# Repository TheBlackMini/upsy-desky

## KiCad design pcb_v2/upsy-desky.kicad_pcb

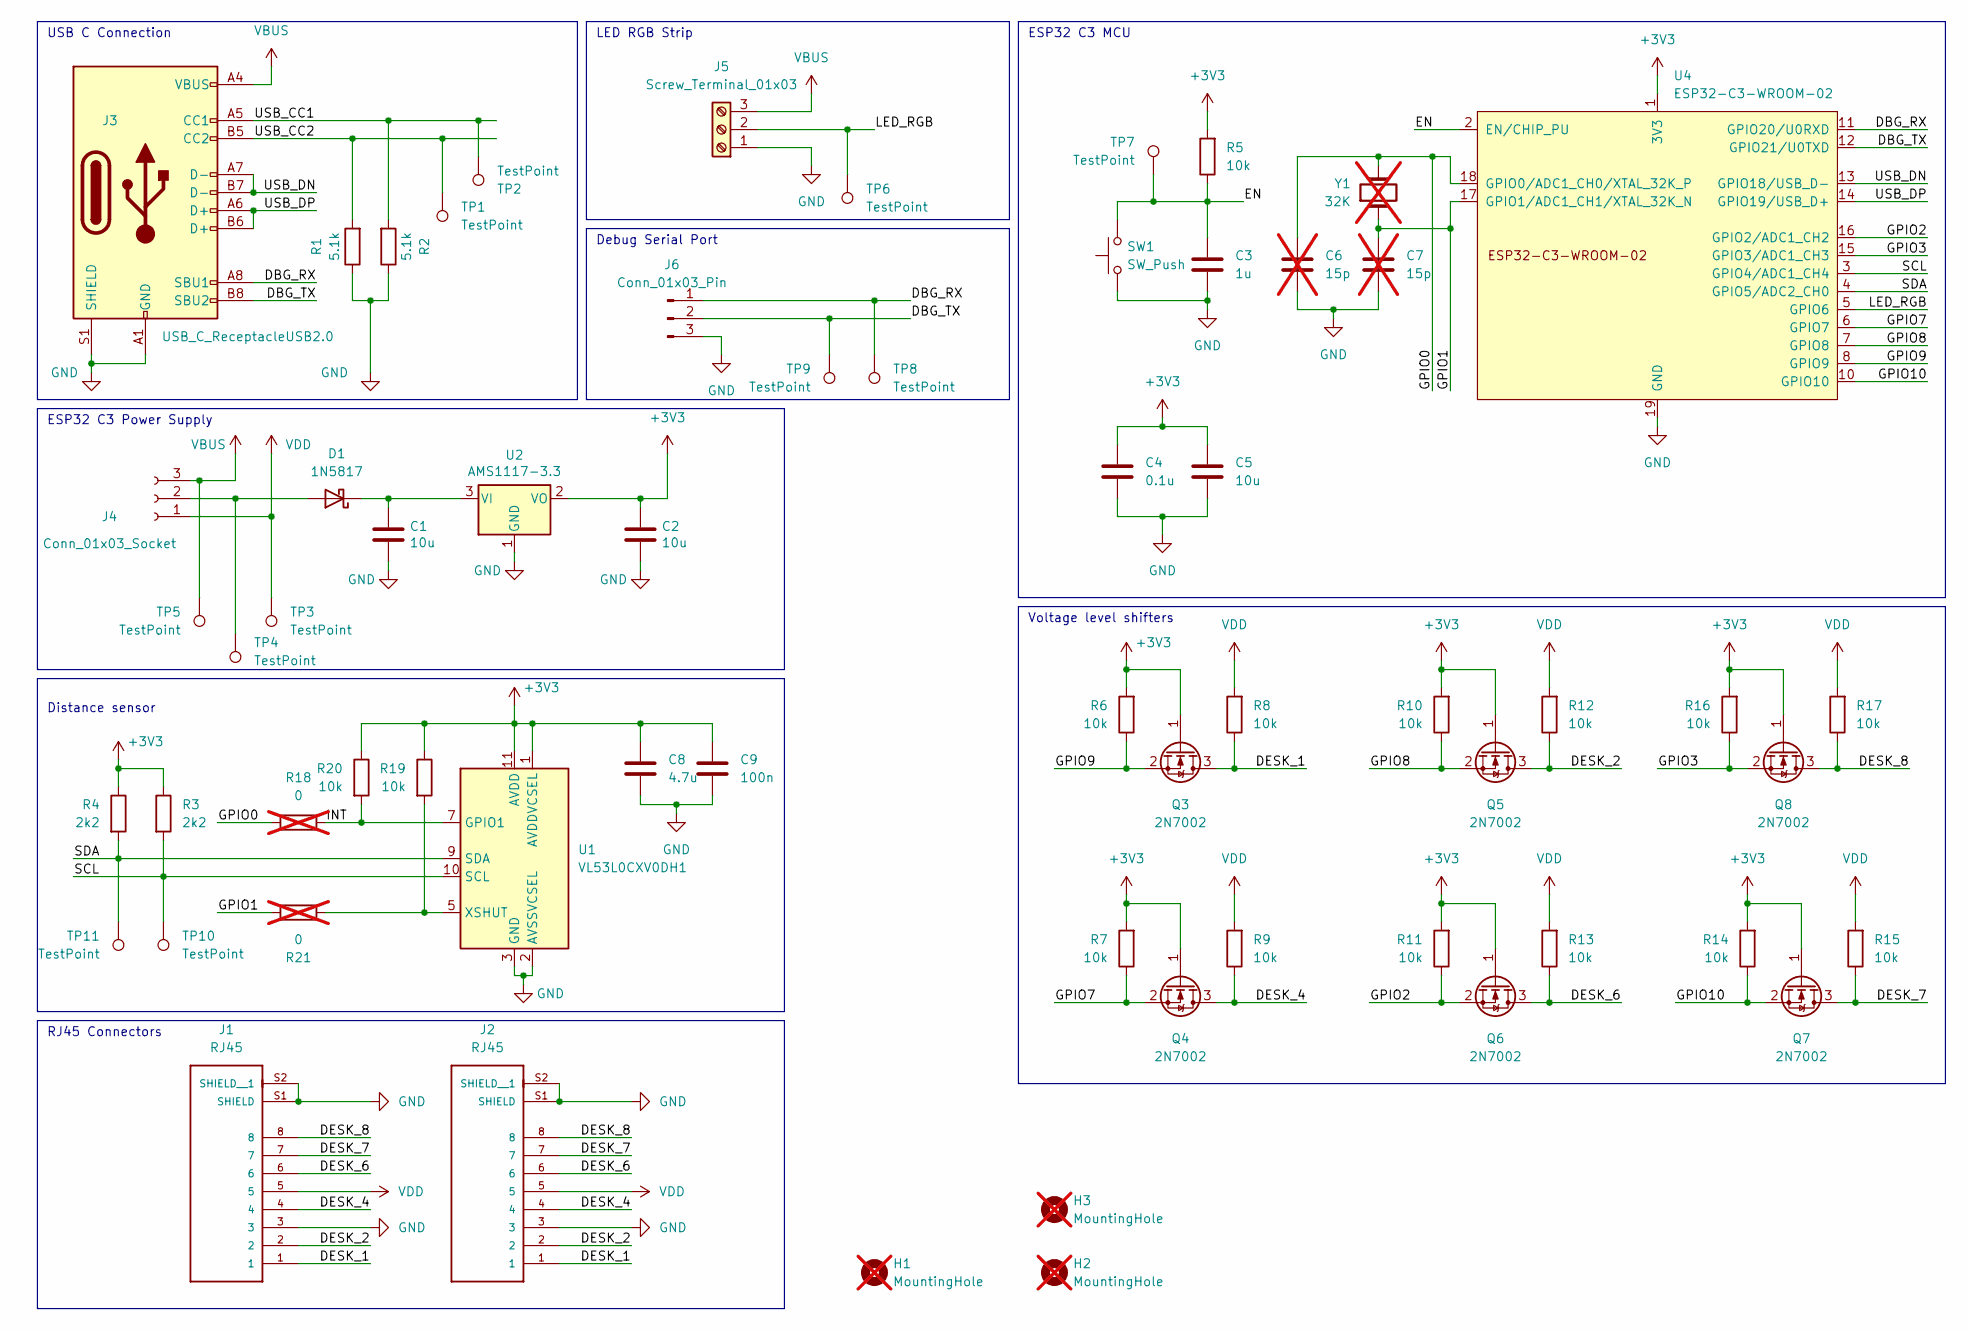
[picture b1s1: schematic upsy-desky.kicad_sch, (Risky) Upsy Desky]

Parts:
C1, C2, C5: 10u; C_0402_1005Metric; MPN GRM155R60J106ME05J; LCSC C15525
C3: 1u; C_0402_1005Metric; MPN 0402W105K100HI; LCSC C52923
C4: 0.1u; C_0402_1005Metric; MPN 0402B104K160HI; LCSC C1525
C6, C7: 15p; C_0402_1005Metric; MPN TCC0402COG150J500AT; not fitted
C8: 4.7u; C_0402_1005Metric; MPN CL05A475MQ5NRNC; DigiKey 1276-1056-2-ND
C9: 100n; C_0402_1005Metric; MPN CC0402KRX7R6BB104; DigiKey 311-1345-2-ND
D1: 1N5817; D_SOD-323; MPN B5817WS-TP; LCSC C191023
H1, H2, H3: MountingHole; MountingHole_2.2mm_M2_Pad; not fitted
J1, J2: RJ45; RJ45_Amphenol_54602-x08_Horizontal; PARTREV 00; LCSC C708595
J3: USB_C_ReceptacleUSB2.0; USB_C_Receptacle_Palconn_UTC16-G; MPN TYPE-C-31-M-12; LCSC C165948
J4: Conn_01x03_Socket; FanPinHeader_1x03_P2.54mm_Vertical; MPN 0022272031; DigiKey WM4112-ND
J5: Screw_Terminal_01x03; TerminalBlock_Altech_AK300-3_P5.00mm; MPN 30-003; DigiKey 1920-30.003-ND
J6: Conn_01x03_Pin; JST_EH_B3B-EH-A_1x03_P2.50mm_Vertical; MPN B3B-EH-A; DigiKey 455-B3B-EH-A-ND
Q3, Q4, Q5, Q6, Q7, Q8: 2N7002; SOT-23; MPN 2N7002; LCSC C8545
R1, R2: 5.1k; R_0402_1005Metric; MPN CR0402JC5K1S01; LCSC C25905
R3, R4: 2k2; R_0402_1005Metric; MPN RC0402FR-072K2L; DigiKey 311-2.20KLRTR-ND
R5, R6, R7, R8, R9, R10, R11, R12, R13, R14, R15, R16, R17: 10k; R_0402_1005Metric; MPN RC0402JR-1310KL; LCSC C25744
R18, R21: 0; R_0402_1005Metric; not fitted
R19, R20: 10k; R_0402_1005Metric; MPN RC0402JR-1310KL; DigiKey 13-RC0402JR-1310KLTR-ND
SW1: SW_Push; SW_Push_1P1T_NO_CK_KMR2; MPN KMR223GLFG; DigiKey 401-1428-2-ND
TP1, TP2, TP3, TP4, TP5, TP6, TP7, TP8, TP9, TP10, TP11: TestPoint; TestPoint_Pad_D1.0mm
U1: VL53L0CXV0DH1; ST_VL53L1x; MPN VL53L0CXV0DH/1; DigiKey 497-16538-2-ND
U2: AMS1117-3.3; SOT-223-3_TabPin2; MPN AMS1117-3.3; LCSC C6186
U4: ESP32-C3-WROOM-02; MPN ESP32-C3-WROOM-02-N4; DigiKey 1965-ESP32-C3-WROOM-02-N4TR-ND
Y1: 32K; Crystal_SMD_2012-2Pin_2.0x1.2mm; MPN 9HT11-32-768KDZF-T; DigiKey 887-1425-2-ND; not fitted

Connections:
+3V3: C2.1, C4.1, C5.1, C8.1, C9.1, Q3.1 (G), Q4.1 (G), Q5.1 (G), Q6.1 (G), Q7.1 (G), Q8.1 (G), R3.1, R4.1, R5.2, R6.2, R7.2, R10.2, R11.2, R14.2, R16.2, R19.1, R20.1, U1.1 (AVDDVCSEL), U1.11 (AVDD), U2.2 (VO), U4.1 (3V3)
/DBG_RX: J3.A8 (SBU1), J6.1, TP8.1, U4.11 (GPIO20/U0RXD)
/DBG_TX: J3.B8 (SBU2), J6.2, TP9.1, U4.12 (GPIO21/U0TXD)
/DESK_1: J1.1, J2.1, Q3.3 (D), R8.1
/DESK_2: J1.2, J2.2, Q5.3 (D), R12.1
/DESK_4: J1.4, J2.4, Q4.3 (D), R9.1
/DESK_6: J1.6, J2.6, Q6.3 (D), R13.1
/DESK_7: J1.7, J2.7, Q7.3 (D), R15.1
/DESK_8: J1.8, J2.8, Q8.3 (D), R17.1
/EN: C3.1, R5.1, SW1.2, TP7.1, U4.2 (EN/CHIP_PU)
/GPIO0: C6.1, R18.2, U4.18 (GPIO0/ADC1_CH0/XTAL_32K_P), Y1.2
/GPIO1: C7.1, R21.2, U4.17 (GPIO1/ADC1_CH1/XTAL_32K_N), Y1.1
/GPIO2: Q6.2 (S), R11.1, U4.16 (GPIO2/ADC1_CH2)
/GPIO3: Q8.2 (S), R16.1, U4.15 (GPIO3/ADC1_CH3)
/GPIO7: Q4.2 (S), R7.1, U4.6 (GPIO7)
/GPIO8: Q5.2 (S), R10.1, U4.7 (GPIO8)
/GPIO9: Q3.2 (S), R6.1, U4.8 (GPIO9)
/GPIO10: Q7.2 (S), R14.1, U4.10 (GPIO10)
/INT: R18.1, R20.2, U1.7 (GPIO1)
/LED_RGB: J5.2, TP6.1, U4.5 (GPIO6)
/SCL: R3.2, TP10.1, U1.10 (SCL), U4.3 (GPIO4/ADC1_CH4)
/SDA: R4.2, TP11.1, U1.9 (SDA), U4.4 (GPIO5/ADC2_CH0)
/USB_CC1: J3.A5 (CC1), R2.2, TP2.1
/USB_CC2: J3.B5 (CC2), R1.2, TP1.1
/USB_DN: J3.A7 (D-), J3.B7 (D-), U4.13 (GPIO18/USB_D-)
/USB_DP: J3.A6 (D+), J3.B6 (D+), U4.14 (GPIO19/USB_D+)
GND: C1.2, C2.2, C3.2, C4.2, C5.2, C6.2, C7.2, C8.2, C9.2, J1.3, J1.S1 (SHIELD), J1.S2 (SHIELD__1), J2.3, J2.S1 (SHIELD), J2.S2 (SHIELD__1), J3.A1 (GND), J3.A12 (GND), J3.B1 (GND), J3.B12 (GND), J3.S1 (SHIELD), J5.1, J6.3, R1.1, R2.1, SW1.1, U1.2 (AVSSVCSEL), U1.3 (GND), U1.4 (GND), U1.6 (GND), U1.12 (GND), U2.1 (GND), U4.9 (GND), U4.19 (GND)
unnamed: D1.2 (A), J4.2, TP4.1
unnamed: C1.1, D1.1 (K), U2.3 (VI)
unnamed: R19.2, R21.1, U1.5 (XSHUT)
VBUS: J3.A4 (VBUS), J3.A9 (VBUS), J3.B4 (VBUS), J3.B9 (VBUS), J4.3, J5.3, TP5.1
VDD: J1.5, J2.5, J4.1, R8.2, R9.2, R12.2, R13.2, R15.2, R17.2, TP3.1

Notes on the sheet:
ESP32 C3 MCU
Debug Serial Port
RJ45 Connectors
USB C Connection
LED RGB Strip
Distance sensor
Voltage level shifters
ESP32 C3 Power Supply

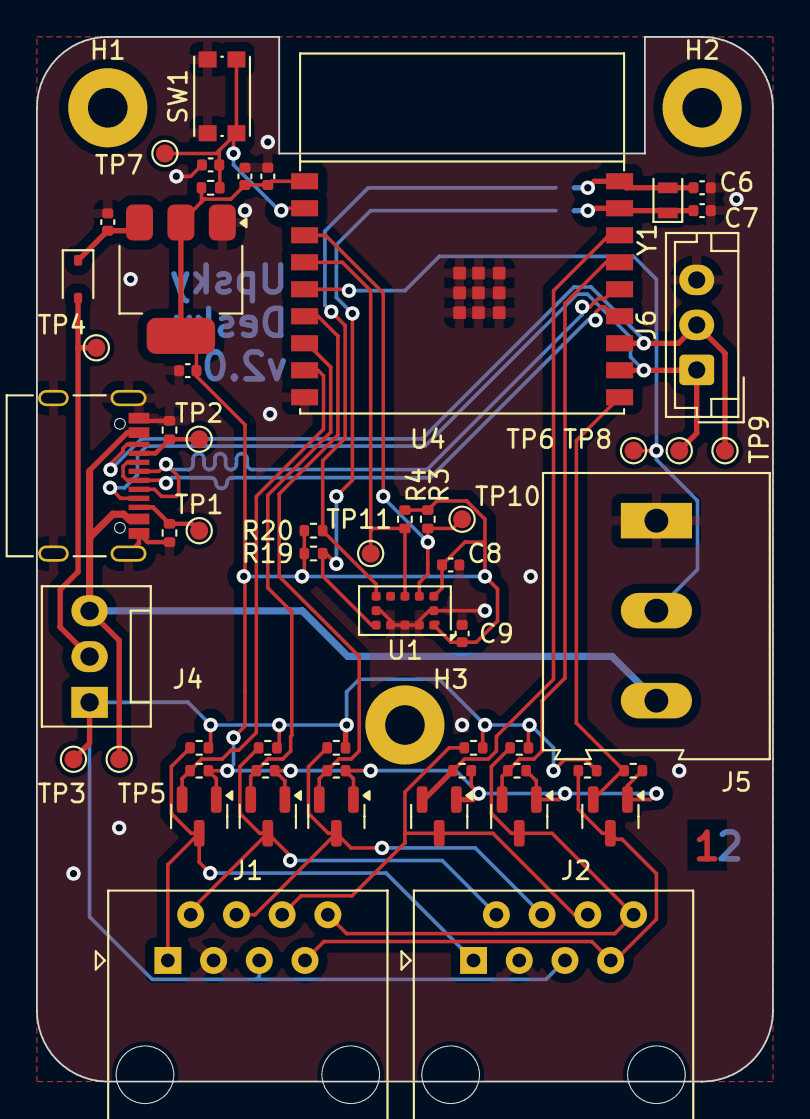
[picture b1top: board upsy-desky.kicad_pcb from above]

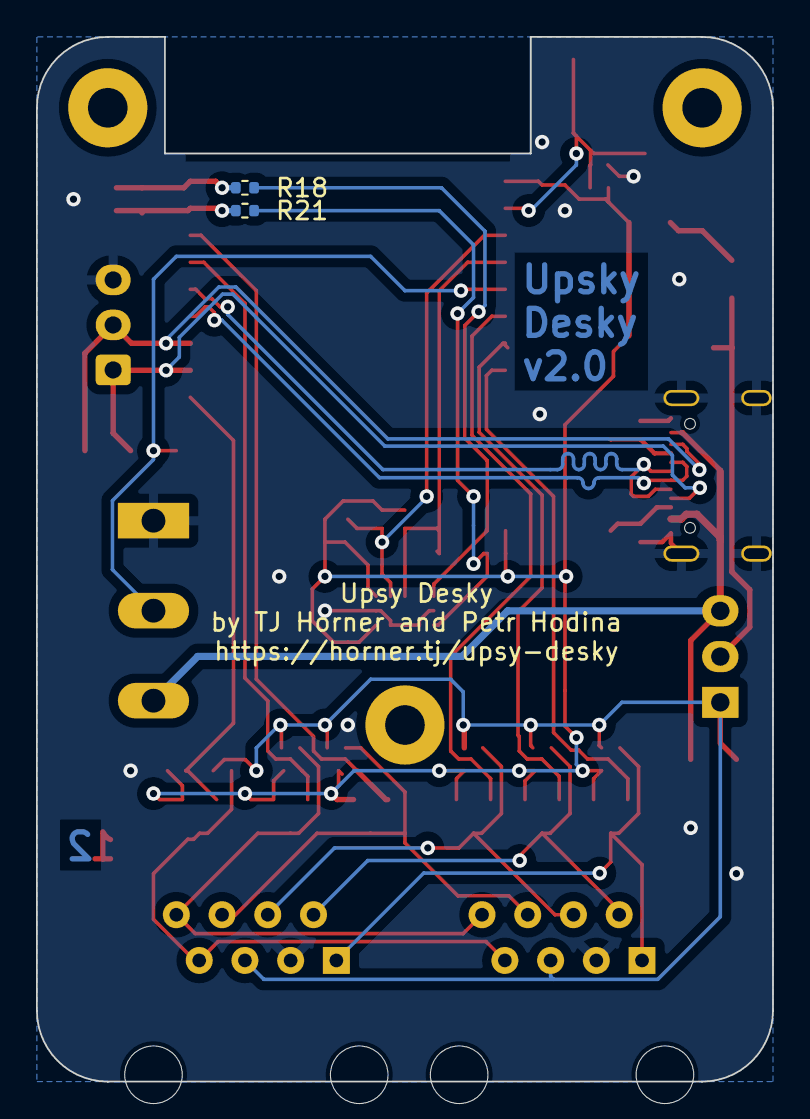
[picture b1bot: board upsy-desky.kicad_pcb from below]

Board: 2 copper layers, 40.9 x 58.0 mm, 62 parts (2 on the bottom side), 32 nets.

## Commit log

2024-06-04 Updated BOM for PCBWay
